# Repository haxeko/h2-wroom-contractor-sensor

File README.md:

# h2-wroom-contractor-sensor

**Cảm biến cửa Matter over Thread, ESP32-H2, cảm biến Hall DRV5032FA, pin CR123A rời, ICD.**
Repo chứa **hai phiên bản phần cứng** dùng chung một mạch nguồn/Hall/nút/LED và **một firmware**:

| | **Bản module** (`wroom`) – khuyên dùng | **Bản chip rời** (`chip`) |
|---|---|---|
| SoC | module **ESP32-H2-WROOM-02C-H4S** (thạch anh, RF, anten nằm trong module) | chip **ESP32-H2FH4S** + thạch anh + mạng RF + anten MIFA in trên PCB |
| PCB | **32 × 20 mm, 2 lớp**, 1.0 mm | 36 × 18 mm, 4 lớp, 1.0 mm, kiểm soát trở kháng 50 Ω |
| BOM lắp ráp | 18 dòng / 27 linh kiện, nhỏ nhất 0402 | 27 dòng / 46 linh kiện, có 0201 |
| RF | không cần tinh chỉnh; 🧪 có thể tận dụng chứng nhận của module | phải tinh chỉnh anten bằng VNA, tự làm chứng nhận vô tuyến |
| Thiết kế KiCad | [`hardware/wroom/`](hardware/wroom/) | [`hardware/chip/`](hardware/chip/) |
| Tài liệu riêng | [`docs/wroom/`](docs/wroom/) | [`docs/chip/`](docs/chip/) |
| Đặt hàng JLCPCB | via 0.6 / 0.3 mm: không phát sinh phí | ⚠️ via 0.4 / 0.2 mm ⇒ JLCPCB đòi thêm phí **4-Wire Kelvin Test**; muốn tránh phải đổi via sang 0.45 / 0.2 mm và đi dây lại (chưa làm) |

Cả hai: ERC 0, DRC 0 vi phạm / 0 kết nối hở / 0 lệch sơ đồ (KiCad 10.0.8). Chưa có phép đo phần cứng nào.

Quy ước trạng thái: ✅ **đã kiểm chứng** (datasheet / mã nguồn SDK / đã build) · 🧪 **cần thử nghiệm** trên phần cứng thật · 💡 **đề xuất** thiết kế.

## Cấu trúc thư mục

```
hardware/
  lib/                     thư viện KiCad dùng chung: mcs.kicad_sym, mcs.pretty (module WROOM, pad dây pin, anten…)
  wroom/                   BẢN MODULE: matter_contact_sensor_wroom.kicad_{pro,sch,pcb,dru}, drc_report.json
    fab/                     file đặt hàng: *-gerber.zip, assembly/*-bom.csv, assembly/*-cpl.csv, PDF, ảnh
  chip/                    BẢN CHIP RỜI: matter_contact_sensor.kicad_{pro,sch,pcb,dru}, drc_report.json
    fab/                     file đặt hàng của bản chip rời
    antenna/                 footprint gốc anten MIFA TI AN043 + 3 biến thể tinh chỉnh
    bom.csv                  BOM đầy đủ có hãng, mã thay thế, giá (bản chip rời; phần chung dùng cho cả hai)
    netlist.csv              netlist mức chân của bản chip rời
firmware/
  matter_contact_sensor/   firmware chung cho cả hai board (ESP-IDF v5.5.5 + esp-matter release/v1.6)
docs/
  README.md                mục lục tài liệu
  common/                  01 tổng quan · 02 nguồn pin · 03 Hall · 08 firmware · 09 tuổi thọ pin · 10 kế hoạch thử · 11 lộ trình
  wroom/                   12 bản module
  chip/                    04 anten RF · 05 sơ đồ · 06 PCB · 07 BOM
tools/
  design_data.py           dữ liệu thiết kế gốc (bản chip rời; phần mạch chung)
  design_data_wroom.py     dữ liệu thiết kế bản module (lấy phần chung từ design_data.py)
  kicad/                   sinh thư viện, sơ đồ, PCB (router), file sản xuất
  battery_life.py, magnet_field.py, coin_cell_buffer.py, cpwg_impedance.py, gen_antenna_variants.py, netlist.py
```

Quy tắc khi sửa:
- **Mạch chung** (nguồn, Hall, nút, LED, đo pin, pad test): sửa ở `tools/design_data.py`, rồi sinh lại **cả hai** board.
- **Riêng bản module**: `tools/design_data_wroom.py`, `tools/kicad/build_pcb_wroom.py`.
- **Riêng bản chip rời**: phần MCU / thạch anh / RF trong `tools/design_data.py`, `tools/kicad/build_pcb.py`.
- **Linh kiện thư viện**: `tools/kicad/gen_libs.py` → `hardware/lib/`.
- Không sửa tay các file trong `fab/`: luôn xuất lại bằng `export_fab.py`.

## Thông số chung

| Hạng mục | Giá trị |
|---|---|
| Firmware | ESP-IDF **v5.5.5** + esp-matter **release/v1.6**: build OK, image 1.50 MB (slot OTA 1.92 MB còn 20 %), cùng một file build cho cả hai board |
| Matter | Contact Sensor (0x0015) + Power Source (CR123A) trên endpoint 1; ICD **SIT** (slow poll 15 s, idle 3600 s) |
| Nguồn | CR123A rời, 2 dây vào J1 → PMOS AO3401A chống ngược cực → **TPS63900** buck-boost 3.2 V (Iq 75 nA) + TPS3839 giám sát |
| Hall | **DRV5032FADBZR** omnipolar 1.6 µA, GPIO10 (LP IO) + EXT1 đảo mức ⇒ phát hiện cả OPEN và CLOSED khi chip ngủ |
| Tuổi thọ pin (ước tính) | **~2.3–2.6 năm** (10–20 lần/ngày), ~2.0–2.5 năm (50–100), ~1.8–2.0 năm (200) với 1500–1700 mAh – 🧪 phải đo |

## Phát hiện quan trọng khi đối chiếu SDK

1. Với esp-matter v1.6, `BooleanState::StateValue` do `BooleanStateCluster` (code-driven) quản lý; `esp_matter::attribute::update()` trả về `ESP_ERR_NOT_SUPPORTED` ⇒ firmware gọi `BooleanStateCluster::SetStateValue()` (tự sinh sự kiện StateChange).
2. Khi bật `CONFIG_PM_POWER_DOWN_PERIPHERAL_IN_LIGHT_SLEEP` (cần cho sàn ~25 µA), đánh thức GPIO thường không còn hoạt động trên ESP32-H2; phải dùng **EXT1 trên LP IO GPIO7–14** ⇒ quyết định chân Hall/nút.
3. ESP-IDF đặt công suất phát 802.15.4 mặc định ở **20 dBm**; firmware hạ xuống 10 dBm ngay từ khung đầu tiên bằng linker wrap của `esp_ieee802154_enable()`.
4. Slow poll của ICD SIT bị connectedhomeip giới hạn ≤ 15 s bằng `static_assert`.
5. Khi chưa ghép nối, BLE giữ thạch anh chính chạy trong light sleep (vài mA thay vì ~25 µA) ⇒ firmware Deep-sleep sau khi cửa sổ commissioning đóng (docs/common/08 §3.6).
6. Pin cúc áo CR2450 không hợp với ESP32-H2: nội trở vượt 20 Ω sau khoảng 250 mAh ⇒ chỉ dùng được ~40 % dung lượng (khoảng nửa năm) (docs/wroom/12 §8).

## Lệnh thường dùng

```bash
# Thư viện + sơ đồ (KiCad 10 + kicad-cli)
python3 tools/kicad/gen_libs.py                          # -> hardware/lib/
python3 tools/kicad/gen_schematic.py --variant wroom     # -> hardware/wroom/
python3 tools/kicad/gen_schematic.py                     # -> hardware/chip/

# PCB: đặt linh kiện + đi dây + đổ đồng + DRC   (pcbnew Python = /usr/bin/python3.12 trên Ubuntu)
/usr/bin/python3.12 tools/kicad/build_pcb_wroom.py       # bản module
/usr/bin/python3.12 tools/kicad/build_pcb.py             # bản chip rời

# File sản xuất: Gerber, khoan, BOM, CPL, PDF, ảnh -> hardware/<board>/fab/
python3 tools/kicad/export_fab.py --variant wroom
python3 tools/kicad/export_fab.py

# Tính toán
python3 tools/battery_life.py --tx-dbm 10 --slow-poll-s 15 --subscribers 2
python3 tools/magnet_field.py
python3 tools/netlist.py          # netlist + kiểm tra ERC đơn giản (bản chip rời)
python3 tools/cpwg_impedance.py   # đường 50 Ω (bản chip rời)

# Firmware (ESP-IDF v5.5.5 + esp-matter release/v1.6 đã export)
cd firmware/matter_contact_sensor && idf.py set-target esp32h2 && idf.py build
```
Các script sinh PCB cho kết quả xác định: chạy lại cho ra đúng hai board đang có trong repo (đã kiểm tra: 285 đoạn đường + via ở bản module, 388 ở bản chip rời).

## Phạm vi và giới hạn

- Mọi con số "thực tế" là ước tính có nguồn, đánh dấu 🧪, kèm quy trình đo; việc cần làm trên mạch mẫu ở docs/wroom/12 §6, docs/chip/06 §10 và docs/common/10.
- Trước khi đặt bản chip rời: kỹ sư layout rà soát và chốt stack-up / trở kháng với nhà sản xuất (docs/chip/06 §10), và xử lý via 0.4 / 0.2 mm nếu đặt ở JLCPCB.
- Dữ liệu commissioning trong firmware là dữ liệu **TEST** của SDK; sản phẩm thật cần VID/PID, DAC, dữ liệu nhà máy và chứng nhận CSA.
- Lịch sử thiết kế trước khi tách repo: [`haxeko/matter-thread-contractor`](https://github.com/haxeko/matter-thread-contractor) (commit `2f9c032`).

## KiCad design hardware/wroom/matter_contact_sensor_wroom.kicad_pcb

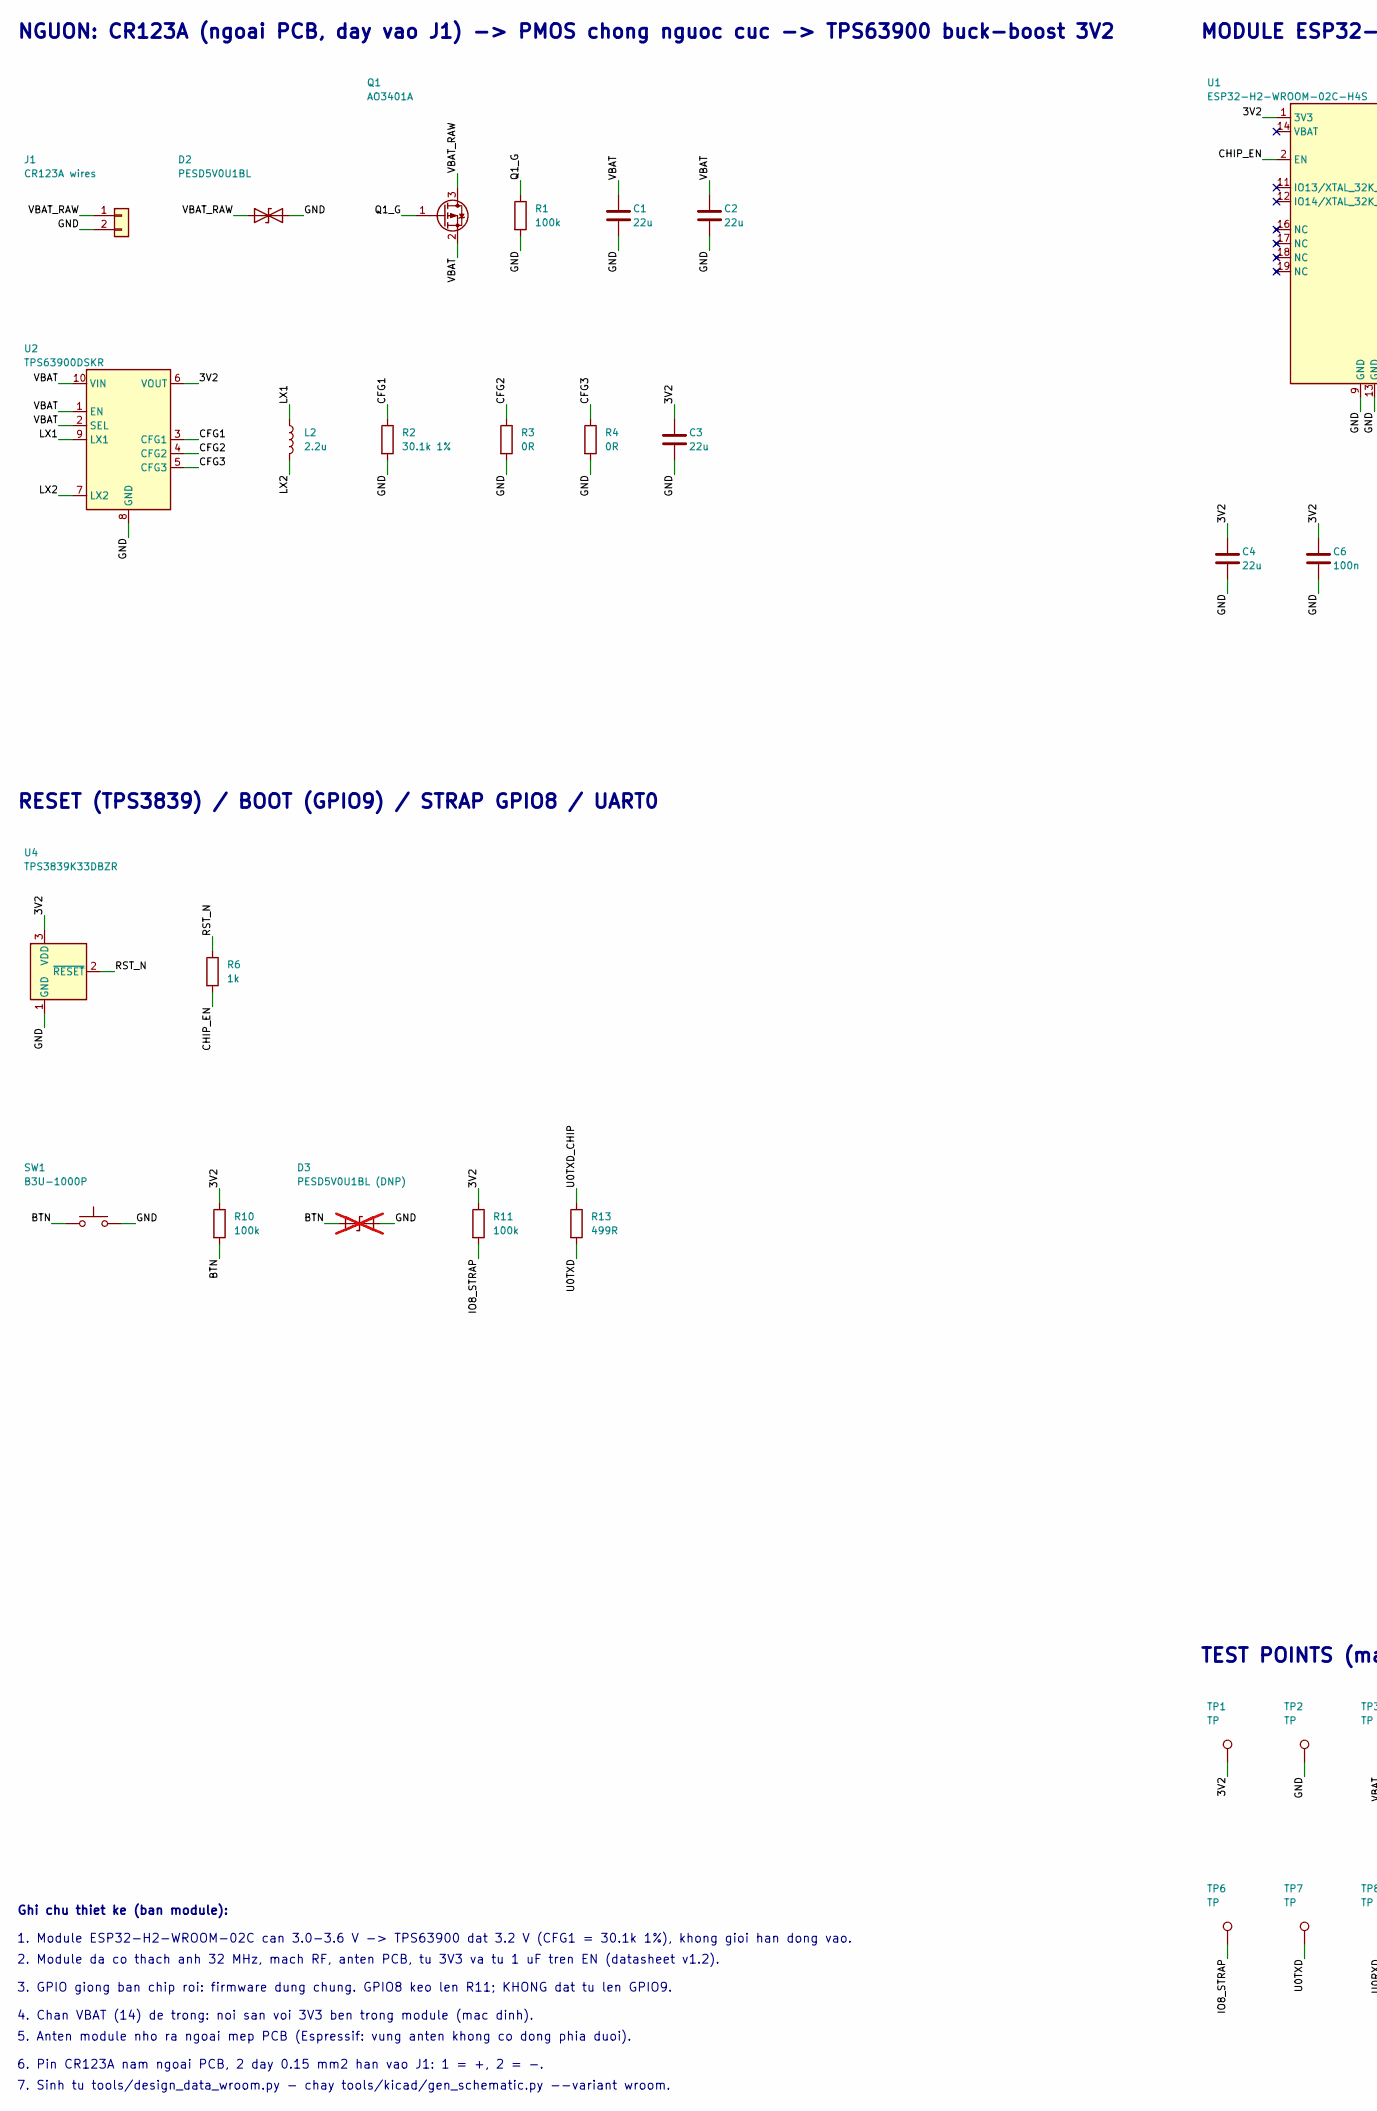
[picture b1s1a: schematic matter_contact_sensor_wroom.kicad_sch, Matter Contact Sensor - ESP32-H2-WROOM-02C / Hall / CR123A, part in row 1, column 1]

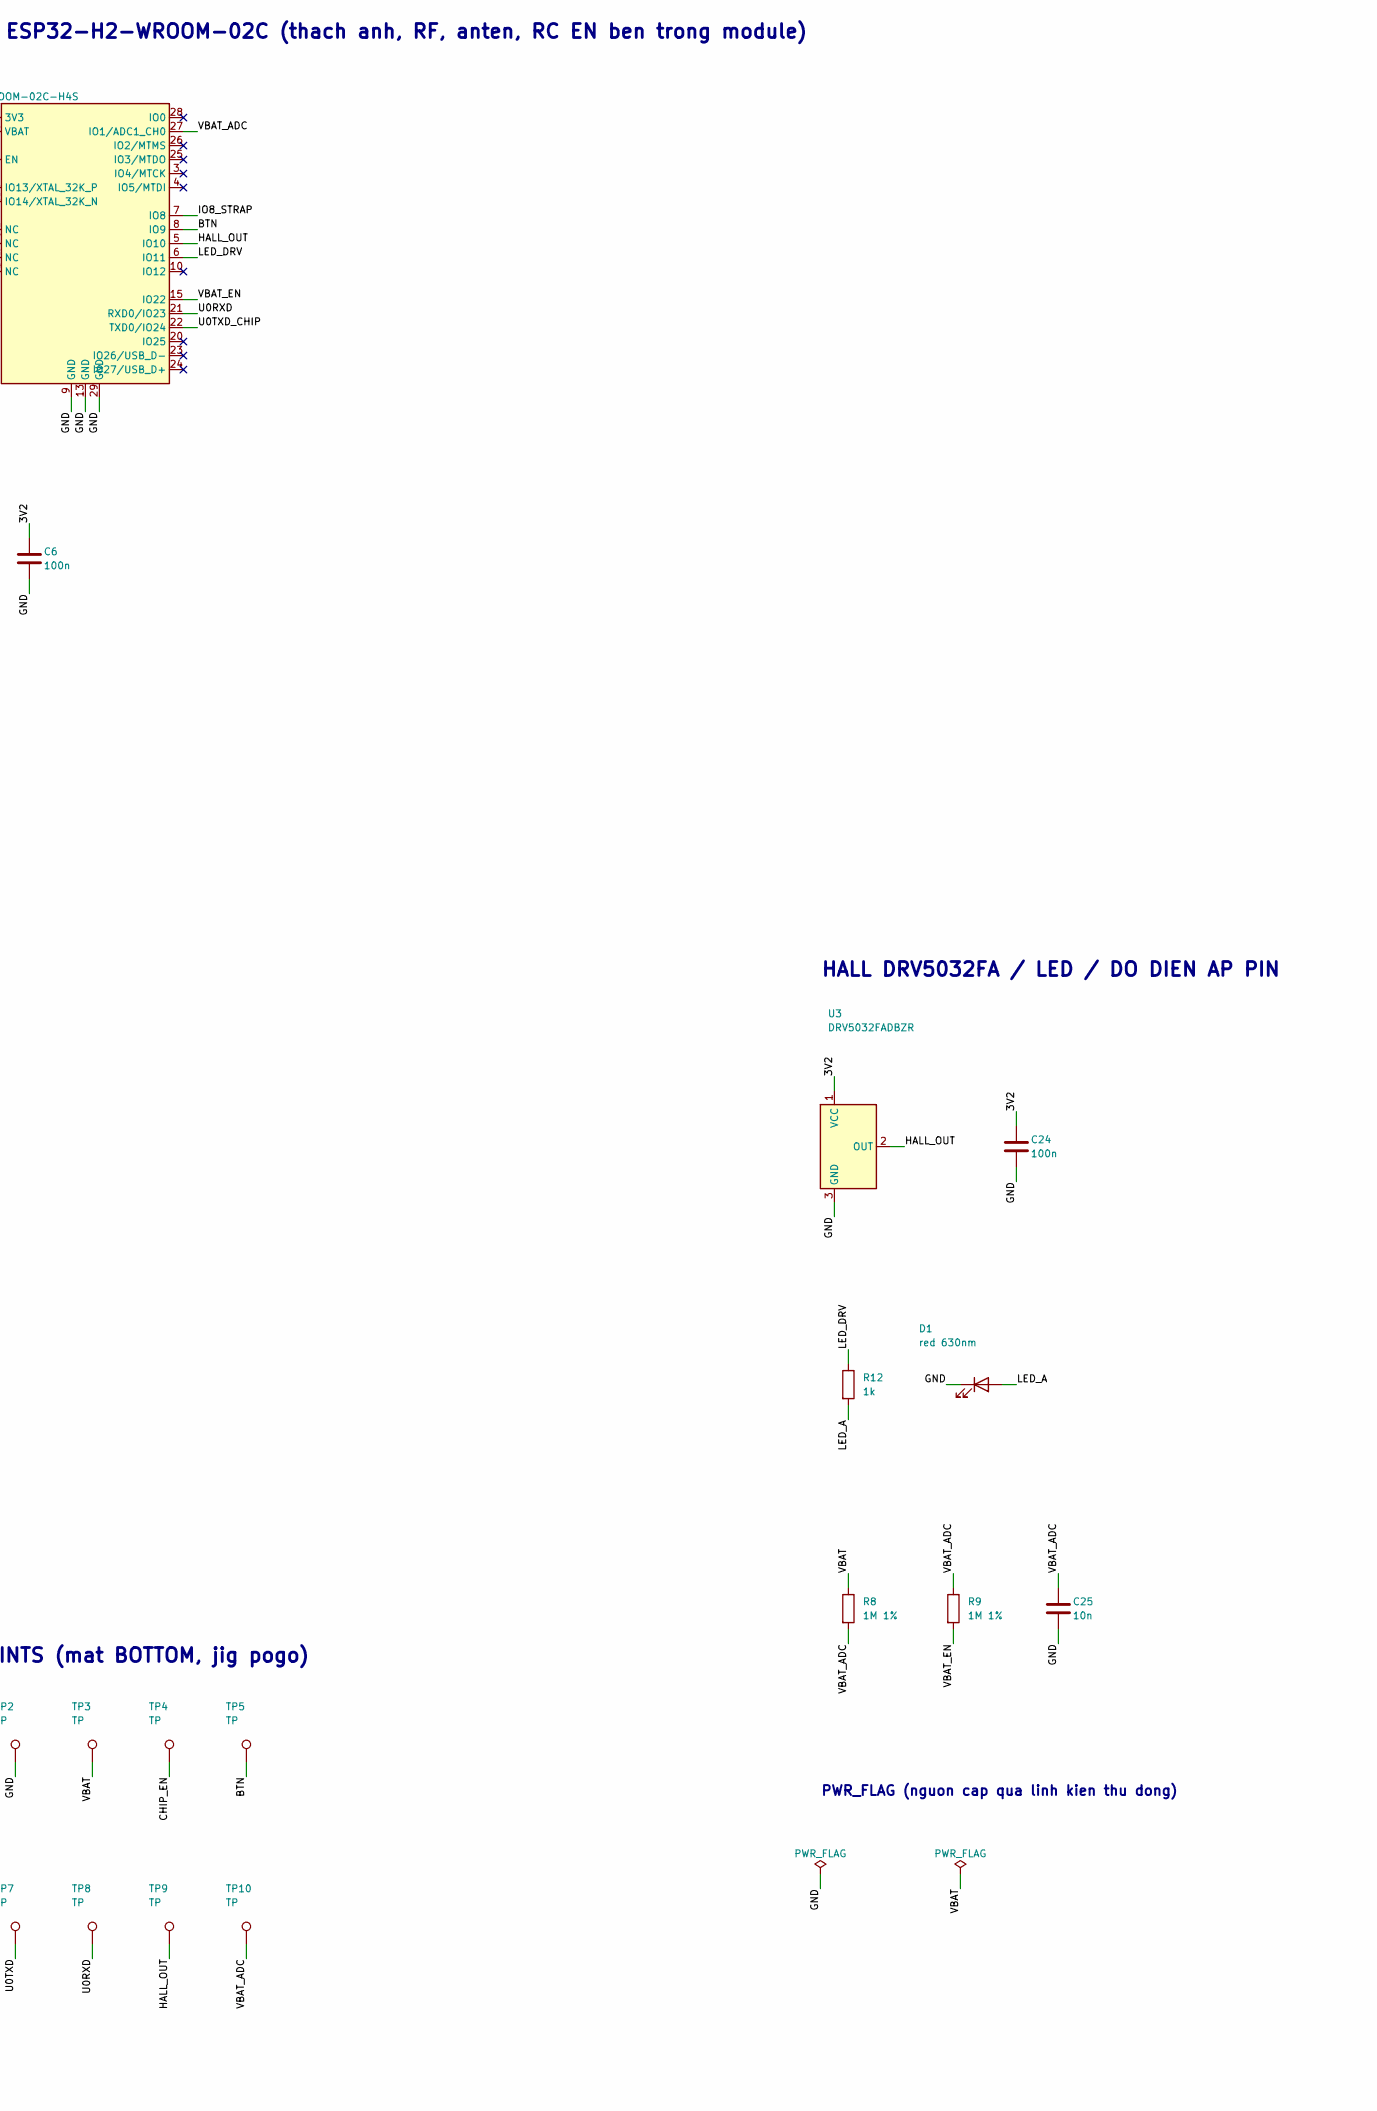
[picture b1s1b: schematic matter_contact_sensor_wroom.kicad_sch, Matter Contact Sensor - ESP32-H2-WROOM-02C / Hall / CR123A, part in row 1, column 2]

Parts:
C1, C2, C3, C4: 22u; C_0603_1608Metric; MPN GRM188R60J226MEA0D
C6, C24: 100n; C_0402_1005Metric; MPN GRM155R71C104KA88D
C25: 10n; C_0402_1005Metric; MPN GRM155R71H103KA88D
D1: red 630nm; LED_0603_1608Metric; MPN APTD1608LSURCK
D2: PESD5V0U1BL; D_SOD-882; MPN PESD5V0U1BL,315
D3: PESD5V0U1BL (DNP); D_SOD-882; MPN PESD5V0U1BL,315; not fitted
J1: CR123A wires; BatteryWires_2x0.15sqmm_P2.54mm_D0.7mm
L2: 2.2u; L_1008_2520Metric; MPN DFE252010F-2R2M
Q1: AO3401A; SOT-23; MPN AO3401A
R1, R10, R11: 100k; R_0402_1005Metric; MPN RC0402FR-07100KL
R2: 30.1k 1%; R_0402_1005Metric; MPN RC0402FR-0730K1L
R3, R4: 0R; R_0402_1005Metric; MPN RC0402JR-070RL
R6, R12: 1k; R_0402_1005Metric; MPN RC0402FR-071KL
R8, R9: 1M 1%; R_0402_1005Metric; MPN RC0402FR-071ML
R13: 499R; R_0402_1005Metric; MPN RC0402FR-07499RL
SW1: B3U-1000P; SW_SPST_B3U-1000P; MPN B3U-1000P
TP1, TP2, TP3, TP4, TP5, TP6, TP7, TP8, TP9, TP10: TP; TestPoint_Pad_D1.0mm
U1: ESP32-H2-WROOM-02C-H4S; ESP32-H2-WROOM-02C; MPN ESP32-H2-WROOM-02C-H4S
U2: TPS63900DSKR; WSON-10-1EP_2.5x2.5mm_P0.5mm_EP1.2x2mm; MPN TPS63900DSKR
U3: DRV5032FADBZR; SOT-23; MPN DRV5032FADBZR
U4: TPS3839K33DBZR; SOT-23; MPN TPS3839K33DBZR

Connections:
/3V2: C3.1, C4.1, C6.1, C24.1, R10.1, R11.1, TP1.1, U1.1 (3V3), U2.6 (VOUT), U3.1 (VCC), U4.3 (VDD)
/BTN: D3.1 (A1), R10.2, SW1.1, TP5.1, U1.8 (IO9)
/CFG1: R2.1, U2.3 (CFG1)
/CFG2: R3.1, U2.4 (CFG2)
/CFG3: R4.1, U2.5 (CFG3)
/CHIP_EN: R6.2, TP4.1, U1.2 (EN)
/GND: C1.2, C2.2, C3.2, C4.2, C6.2, C24.2, C25.2, D1.1 (K), D2.2 (A2), D3.2 (A2), J1.2, R1.2, R2.2, R3.2, R4.2, SW1.2, TP2.1, U1.9 (GND), U1.13 (GND), U1.29 (GND), U2.8 (GND), U2.11 (GND), U3.3 (GND), U4.1 (GND)
/HALL_OUT: TP9.1, U1.5 (IO10), U3.2 (OUT)
/IO8_STRAP: R11.2, TP6.1, U1.7 (IO8)
/LED_A: D1.2 (A), R12.2
/LED_DRV: R12.1, U1.6 (IO11)
/LX1: L2.1, U2.9 (LX1)
/LX2: L2.2, U2.7 (LX2)
/Q1_G: Q1.1 (G), R1.1
/RST_N: R6.1, U4.2 (~RESET)
/U0RXD: TP8.1, U1.21 (RXD0/IO23)
/U0TXD: R13.2, TP7.1
/U0TXD_CHIP: R13.1, U1.22 (TXD0/IO24)
/VBAT: C1.1, C2.1, Q1.2 (S), R8.1, TP3.1, U2.1 (EN), U2.2 (SEL), U2.10 (VIN)
/VBAT_ADC: C25.1, R8.2, R9.1, TP10.1, U1.27 (IO1/ADC1_CH0)
/VBAT_EN: R9.2, U1.15 (IO22)
/VBAT_RAW: D2.1 (A1), J1.1, Q1.3 (D)

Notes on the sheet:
NGUON: CR123A (ngoai PCB, day vao J1) -> PMOS chong nguoc cuc -> TPS63900 buck-boost 3V2
MODULE ESP32-H2-WROOM-02C (thach anh, RF, anten, RC EN ben trong module)
RESET (TPS3839) / BOOT (GPIO9) / STRAP GPIO8 / UART0
HALL DRV5032FA / LED / DO DIEN AP PIN
TEST POINTS (mat BOTTOM, jig pogo)
PWR_FLAG (nguon cap qua linh kien thu dong)
Ghi chu thiet ke (ban module):
1. Module ESP32-H2-WROOM-02C can 3.0-3.6 V -> TPS63900 dat 3.2 V (CFG1 = 30.1k 1%), khong gioi han dong vao.
2. Module da co thach anh 32 MHz, mach RF, anten PCB, tu 3V3 va tu 1 uF tren EN (datasheet v1.2).
3. GPIO giong ban chip roi: firmware dung chung. GPIO8 keo len R11; KHONG dat tu len GPIO9.
4. Chan VBAT (14) de trong: noi san voi 3V3 ben trong module (mac dinh).
5. Anten module nho ra ngoai mep PCB (Espressif: vung anten khong co dong phia duoi).
6. Pin CR123A nam ngoai PCB, 2 day 0.15 mm2 han vao J1: 1 = +, 2 = -.
7. Sinh tu tools/design_data_wroom.py - chay tools/kicad/gen_schematic.py --variant wroom.

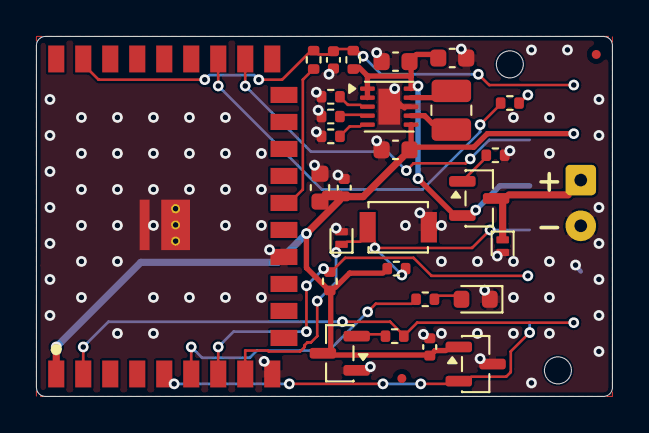
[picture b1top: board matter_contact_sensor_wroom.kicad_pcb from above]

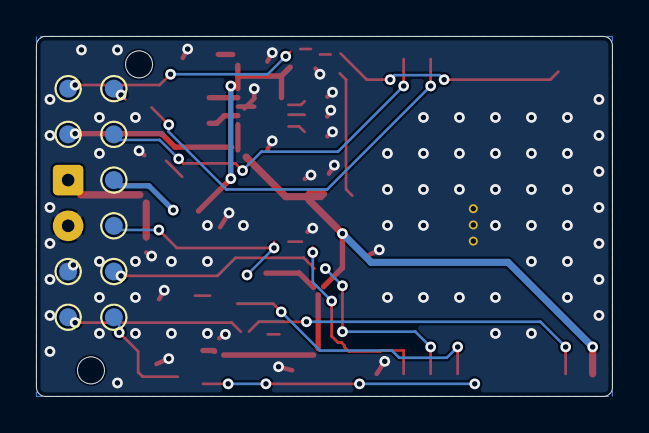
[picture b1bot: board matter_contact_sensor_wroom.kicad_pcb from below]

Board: 2 copper layers, 32.0 x 20.0 mm, 43 parts (10 on the bottom side), 22 nets.

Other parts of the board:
FID1, FID2: Fiducial_0.5mm_Mask1mm
H1, H2: ToolingHole_NPTH_1.5mm

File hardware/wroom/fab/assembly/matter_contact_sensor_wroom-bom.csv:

Comment,Designator,Footprint,Quantity,Manufacturer,MPN,LCSC Part #
22u,"C1,C2,C3,C4",C_0603_1608Metric,4,Murata,GRM188R60J226MEA0D,C77042
100n,"C6,C24",C_0402_1005Metric,2,Murata,GRM155R71C104KA88D,
10n,C25,C_0402_1005Metric,1,Murata,GRM155R71H103KA88D,
red 630nm,D1,LED_0603_1608Metric,1,Kingbright,APTD1608LSURCK,
PESD5V0U1BL,D2,D_SOD-882,1,Nexperia,"PESD5V0U1BL,315",
2.2u,L2,L_1008_2520Metric,1,Murata,DFE252010F-2R2M,
AO3401A,Q1,SOT-23,1,Alpha & Omega,AO3401A,C15127
100k,"R1,R10,R11",R_0402_1005Metric,3,Yageo,RC0402FR-07100KL,
30.1k 1%,R2,R_0402_1005Metric,1,Yageo,RC0402FR-0730K1L,
0R,"R3,R4",R_0402_1005Metric,2,Yageo,RC0402JR-070RL,
1k,"R6,R12",R_0402_1005Metric,2,Yageo,RC0402FR-071KL,
1M 1%,"R8,R9",R_0402_1005Metric,2,Yageo,RC0402FR-071ML,
510R,R13,R_0402_1005Metric,1,Yageo,RC0402JR-07510RL,
B3U-1000P,SW1,SW_SPST_B3U-1000P,1,Omron,B3U-1000P,C231329
ESP32-H2-WROOM-02C-H4S,U1,ESP32-H2-WROOM-02C,1,Espressif,ESP32-H2-WROOM-02C-H4S,
TPS63900DSKR,U2,WSON-10-1EP_2.5x2.5mm_P0.5mm_EP1.2x2mm,1,Texas Instruments,TPS63900DSKR,C1518762
DRV5032FADBZR,U3,SOT-23,1,Texas Instruments,DRV5032FADBZR,
TPS3839K33DBZR,U4,SOT-23,1,Texas Instruments,TPS3839K33DBZR,

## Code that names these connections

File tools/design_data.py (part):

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

ESP32_PINS = {
    "1": "3V2", "2": "3V2", "3": "NC_GPIO0", "4": "VBAT_ADC", "5": "NC_GPIO2", "6": "NC_GPIO3",
    "7": "NC_GPIO4", "8": "NC_GPIO5", "9": "3V2", "10": "IO8_STRAP", "11": "BTN", "12": "HALL_OUT",
    "13": "LED_DRV", "14": "NC_GPIO12", "15": "X32K_P", "16": "X32K_N", "17": "CHIP_EN",
    "18": "VBAT_PIN18", "19": "3V2", "20": "3V2", "21": "VBAT_EN", "22": "U0RXD", "23": "U0TXD_CHIP",
    "24": "NC_GPIO25", "25": "NC_GPIO26", "26": "NC_GPIO27", "27": "3V2", "28": "XTAL_N", "29": "XTAL_P",
    "30": "3V2", "31": "3V2", "32": "LNA_IN", "33": "GND",
}
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    C("C13", "100n", "CHIP_EN", "GND", "reset", C0402, "GRM155R71C104KA88D"),
    R("R7", "10k", "3V2", "CHIP_EN", "reset", "RC0402FR-0710KL", dnp=True, desc="RC reset fallback"),
    C("C14", "1u", "CHIP_EN", "GND", "reset", C0402, "GRM155R61A105KE15D", dnp=True, desc="RC reset fallback"),
    R("R10", "100k", "3V2", "BTN", "reset", "RC0402FR-07100KL", desc="GPIO9 strap pull-up"),
    Part("SW1", "Switch:SW_Push", "Button_Switch_SMD:SW_SPST_B3U-1000P", "B3U-1000P", {"1": "BTN", "2": "GND"},
         "reset", "B3U-1000P", "Omron", description="Commissioning / reset / BOOT button"),
    Part("D3", "Device:D_TVS", "Diode_SMD:D_SOD-882", "PESD5V0U1BL", {"1": "BTN", "2": "GND"}, "reset",
         "PESD5V0U1BL,315", "Nexperia", dnp=True, description="ESD on button (optional)"),
    R("R11", "100k", "3V2", "IO8_STRAP", "reset", "RC0402FR-07100KL", desc="GPIO8 strap pull-up (download mode)"),
    R("R13", "499R", "U0TXD_CHIP", "U0TXD", "reset", "RC0402FR-07499RL", desc="U0TXD harmonic suppression"),
    # ------------------------------------------------------------------ clocks
    L("L3", "24n", "XTAL_P", "XTAL_P_X", "xtal", L0402, "LQW15AN24NG00D"),
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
